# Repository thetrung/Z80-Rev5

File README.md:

# Z80-Rev5 
Rev.5 of Z80 system designed with STC8H8K64U, 512K SRAM/EEPROM.

### Note
I have never had a real working Z80 before so this board is designed to test that if I can get one.

### 3D Preview 

### Placement (SilkScreen)

### Schematic

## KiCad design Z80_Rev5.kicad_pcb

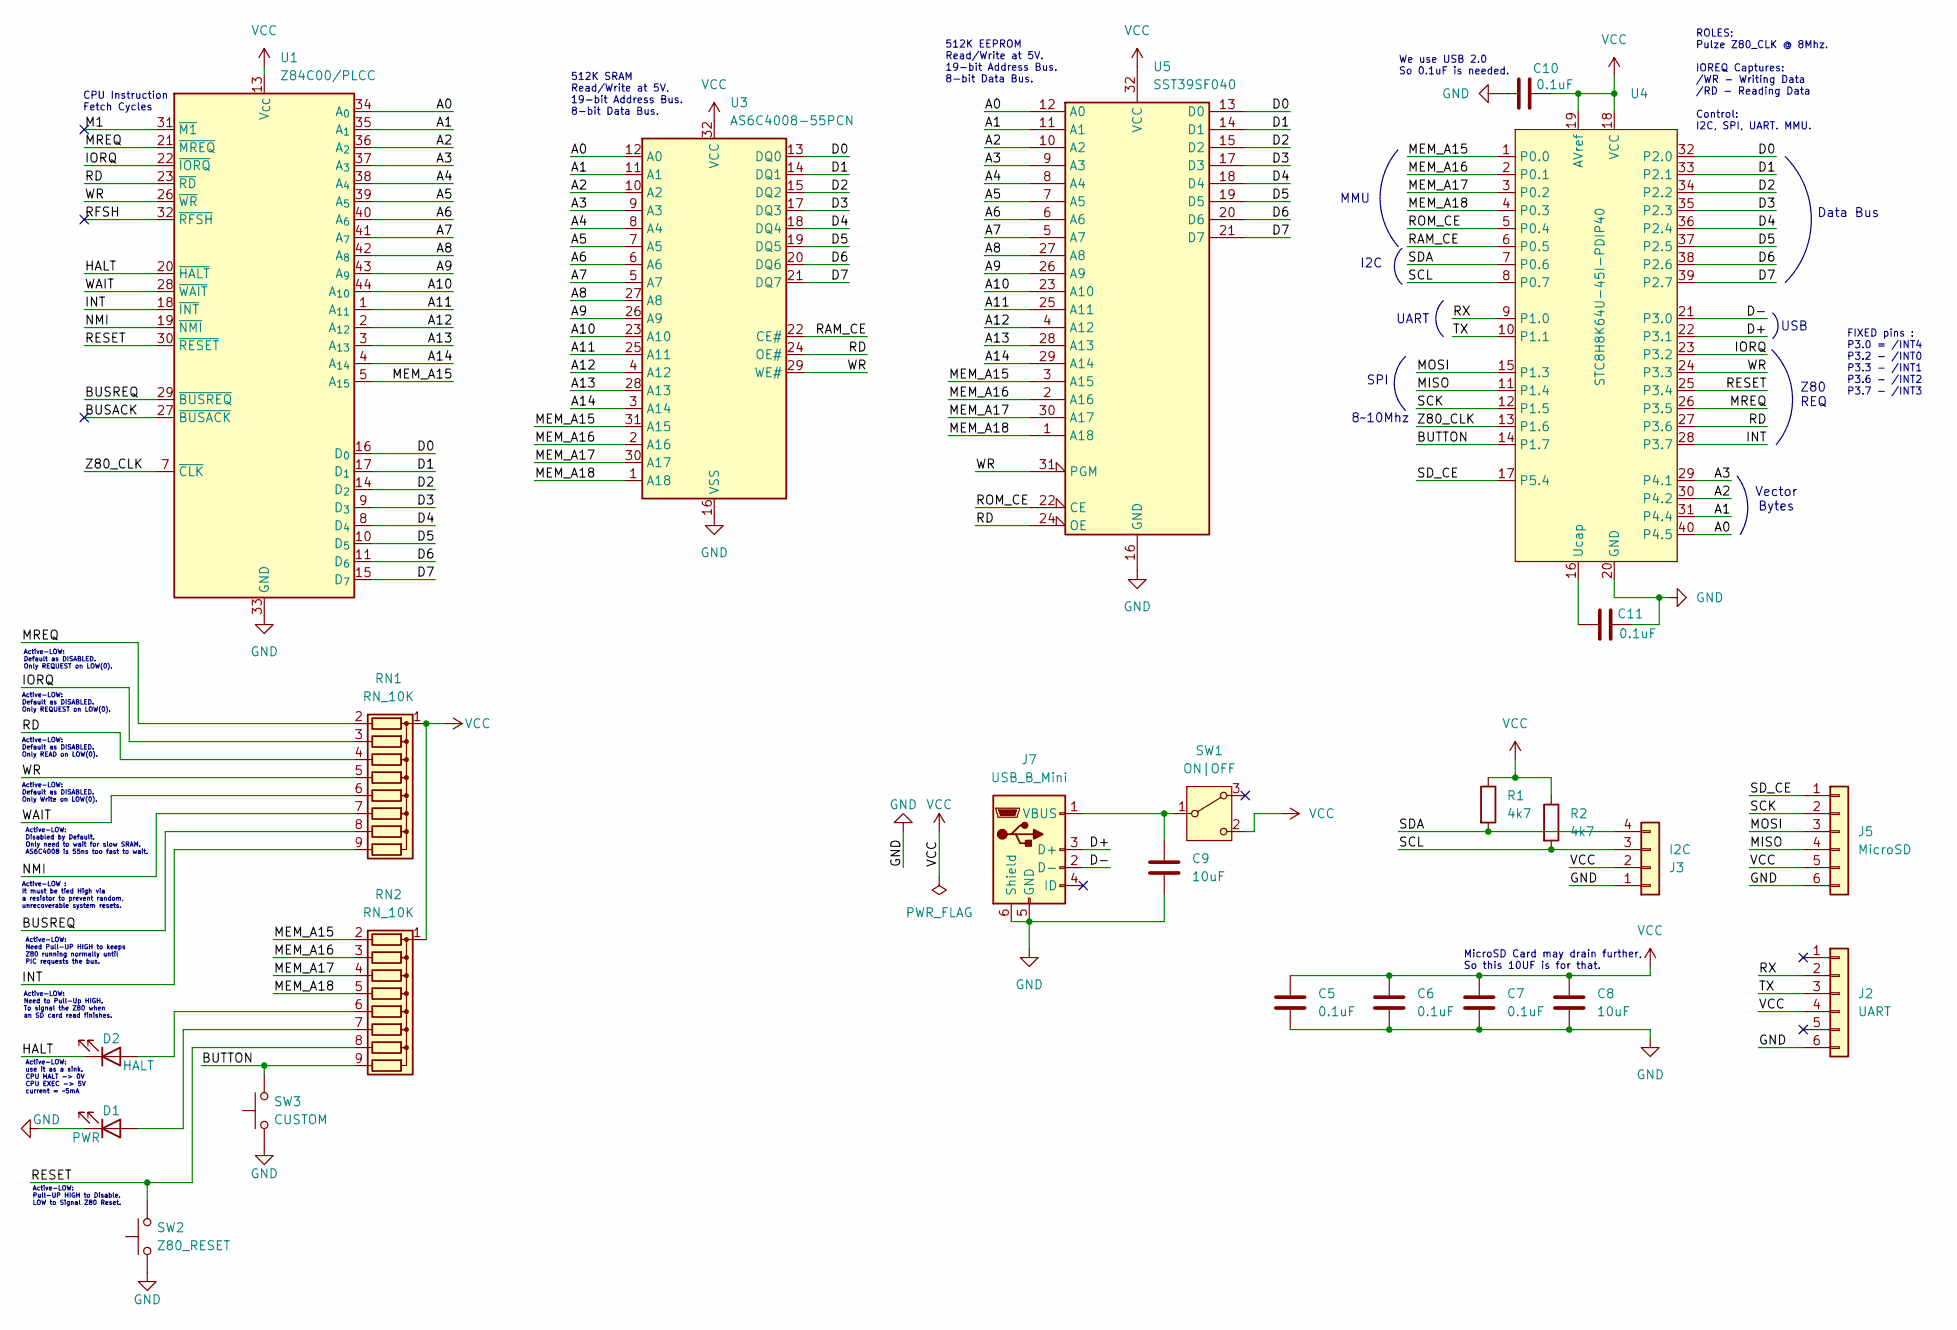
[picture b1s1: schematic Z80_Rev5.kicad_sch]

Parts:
C5, C6, C7, C10, C11: 0.1uF; C_Disc_D3.4mm_W2.1mm_P2.50mm
C8, C9: 10uF; C_Radial_D4.0mm_H5.0mm_P1.50mm
D1: PWR; LED_D3.0mm
D2: HALT; LED_D3.0mm
J2: UART; PinHeader_1x06_P2.54mm_Vertical
J3: I2C; PinHeader_1x04_P2.54mm_Vertical
J5: MicroSD; PinHeader_1x06_P2.54mm_Vertical
J7: USB_B_Mini; USB_MINI_B_90_Angled
R1, R2: 4k7; R_Axial_DIN0207_L6.3mm_D2.5mm_P10.16mm_Horizontal
RN1, RN2: RN_10K; R_Array_SIP9
SW1: ON|OFF; SW_Slide-03_Wuerth-WS-SLTV_10x2.5x6.4_P2.54mm
SW2: Z80_RESET; SW_PUSH_6mm
SW3: CUSTOM; SW_PUSH_6mm
U1: Z84C00/PLCC; PLCC-44_THT-Socket
U3: AS6C4008-55PCN; DIP-32_W15.24mm
U4: STC8H8K64U-45I-PDIP40; DIP-40_W15.24mm
U5: SST39SF040; DIP-32_W15.24mm_Socket

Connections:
/A0: U1.34 (A_{0}), U3.12 (A0), U4.40 (P4.5), U5.12 (A0)
/A1: U1.35 (A_{1}), U3.11 (A1), U4.31 (P4.4), U5.11 (A1)
/A2: U1.36 (A_{2}), U3.10 (A2), U4.30 (P4.2), U5.10 (A2)
/A3: U1.37 (A_{3}), U3.9 (A3), U4.29 (P4.1), U5.9 (A3)
/A4: U1.38 (A_{4}), U3.8 (A4), U5.8 (A4)
/A5: U1.39 (A_{5}), U3.7 (A5), U5.7 (A5)
/A6: U1.40 (A_{6}), U3.6 (A6), U5.6 (A6)
/A7: U1.41 (A_{7}), U3.5 (A7), U5.5 (A7)
/A8: U1.42 (A_{8}), U3.27 (A8), U5.27 (A8)
/A9: U1.43 (A_{9}), U3.26 (A9), U5.26 (A9)
/A10: U1.44 (A_{10}), U3.23 (A10), U5.23 (A10)
/A11: U1.1 (A_{11}), U3.25 (A11), U5.25 (A11)
/A12: U1.2 (A_{12}), U3.4 (A12), U5.4 (A12)
/A13: U1.3 (A_{13}), U3.28 (A13), U5.28 (A13)
/A14: U1.4 (A_{14}), U3.3 (A14), U5.29 (A14)
/BUSACK: U1.27 (~BUSACK)
/BUSREQ: RN1.8 (R7), U1.29 (~BUSREQ)
/BUTTON: RN2.9 (R8), SW3.2, U4.14 (P1.7)
/D0: U1.16 (D_{0}), U3.13 (DQ0), U4.32 (P2.0), U5.13 (D0)
/D1: U1.17 (D_{1}), U3.14 (DQ1), U4.33 (P2.1), U5.14 (D1)
/D2: U1.14 (D_{2}), U3.15 (DQ2), U4.34 (P2.2), U5.15 (D2)
/D3: U1.9 (D_{3}), U3.17 (DQ3), U4.35 (P2.3), U5.17 (D3)
/D4: U1.8 (D_{4}), U3.18 (DQ4), U4.36 (P2.4), U5.18 (D4)
/D5: U1.10 (D_{5}), U3.19 (DQ5), U4.37 (P2.5), U5.19 (D5)
/D6: U1.11 (D_{6}), U3.20 (DQ6), U4.38 (P2.6), U5.20 (D6)
/D7: U1.15 (D_{7}), U3.21 (DQ7), U4.39 (P2.7), U5.21 (D7)
/D+: J7.3 (D+), U4.22 (P3.1)
/D-: J7.2 (D-), U4.21 (P3.0)
/HALT: D2.1 (K), U1.20 (~HALT)
/INT: RN1.9 (R8), U1.18 (~INT), U4.28 (P3.7)
/IORQ: RN1.3 (R2), U1.22 (~IORQ), U4.23 (P3.2)
/M1: U1.31 (~M1)
/MEM_A15: RN2.2 (R1), U1.5 (A_{15}), U3.31 (A15), U4.1 (P0.0), U5.3 (A15)
/MEM_A16: RN2.3 (R2), U3.2 (A16), U4.2 (P0.1), U5.2 (A16)
/MEM_A17: RN2.4 (R3), U3.30 (A17), U4.3 (P0.2), U5.30 (A17)
/MEM_A18: RN2.5 (R4), U3.1 (A18), U4.4 (P0.3), U5.1 (A18)
/MISO: J5.4, U4.11 (P1.4)
/MOSI: J5.3, U4.15 (P1.3)
/MREQ: RN1.2 (R1), U1.21 (~MREQ), U4.26 (P3.5)
/NMI: RN1.7 (R6), U1.19 (~NMI)
/RAM_CE: U3.22 (CE#), U4.6 (P0.5)
/RD: RN1.4 (R3), U1.23 (~RD), U3.24 (OE#), U4.27 (P3.6), U5.24 (OE)
/RESET: RN2.8 (R7), SW2.2, U1.30 (~RESET), U4.25 (P3.4)
/RFSH: U1.32 (~RFSH)
/ROM_CE: U4.5 (P0.4), U5.22 (CE)
/RX: J2.2, U4.9 (P1.0)
/SCK: J5.2, U4.12 (P1.5)
/SCL: J3.3, R2.2, U4.8 (P0.7)
/SDA: J3.4, R1.2, U4.7 (P0.6)
/SD_CE: J5.1, U4.17 (P5.4)
/TX: J2.3, U4.10 (P1.1)
/WAIT: RN1.6 (R5), U1.28 (~WAIT)
/WR: RN1.5 (R4), U1.26 (~WR), U3.29 (WE#), U4.24 (P3.3), U5.31 (PGM)
/Z80_CLK: U1.7 (~CLK), U4.13 (P1.6)
GND: C5.1, C6.1, C7.1, C8.1, C9.1, C10.2, C11.2, D1.1 (K), J2.6, J3.1, J5.6, J7.5 (GND), J7.6 (Shield), SW2.1, SW3.1, U1.33 (GND), U3.16 (VSS), U4.20 (GND), U5.16 (GND)
unnamed: D1.2 (A), RN2.7 (R6)
unnamed: D2.2 (A), RN2.6 (R5)
unnamed: C9.2, J7.1 (VBUS), SW1.1 (B)
unnamed: C11.1, U4.16 (Ucap)
VCC: C5.2, C6.2, C7.2, C8.2, C10.1, J2.4, J3.2, J5.5, R1.1, R2.1, RN1.1 (common), RN2.1 (common), SW1.2 (C), U1.13 (V_{CC}), U3.32 (VCC), U4.18 (VCC), U4.19 (AVref), U5.32 (VCC)

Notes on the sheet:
Active-LOW: Default as DISABLED. Only REQUEST on LOW(0).
Active-LOW: Need to Pull-Up HIGH. To signal the Z80 when an SD card read finishes.
Data Bus
512K SRAM Read/Write at 5V. 19-bit Address Bus. 8-bit Data Bus.
Active-LOW: use it as a sink. CPU HALT -> 0V CPU EXEC -> 5V current = ~5mA
Active-LOW: Default as DISABLED. Only READ on LOW(0).
UART
MMU
ROLES: Pulze Z80_CLK @ 8Mhz. IOREQ Captures: /WR - Writing Data /RD - Reading Data Control: I2C, SPI, UART. MMU.
512K EEPROM Read/Write at 5V. 19-bit Address Bus. 8-bit Data Bus.
Active-LOW: Disabled by Default. Only need to wait for slow SRAM. AS6C4008 is 55ns too fast to wait.
Active-LOW: Need Pull-UP HIGH to keeps Z80 running normally until PIC requests the bus.
Vector Bytes
MicroSD Card may drain further, So this 10UF is for that.
Active-LOW : It must be tied High via a resistor to prevent random, unrecoverable system resets.
Active-LOW: Pull-UP HIGH to Disable. LOW to Signal Z80 Reset.
Active-LOW: Default as DISABLED. Only Write on LOW(0).
Z80 REQ
FIXED pins : P3.0 = /INT4 P3.2 - /INT0 P3.3 - /INT1 P3.6 - /INT2 P3.7 - /INT3
8~10Mhz
We use USB 2.0 So 0.1uF is needed.
CPU Instruction Fetch Cycles
USB
I2C
SPI

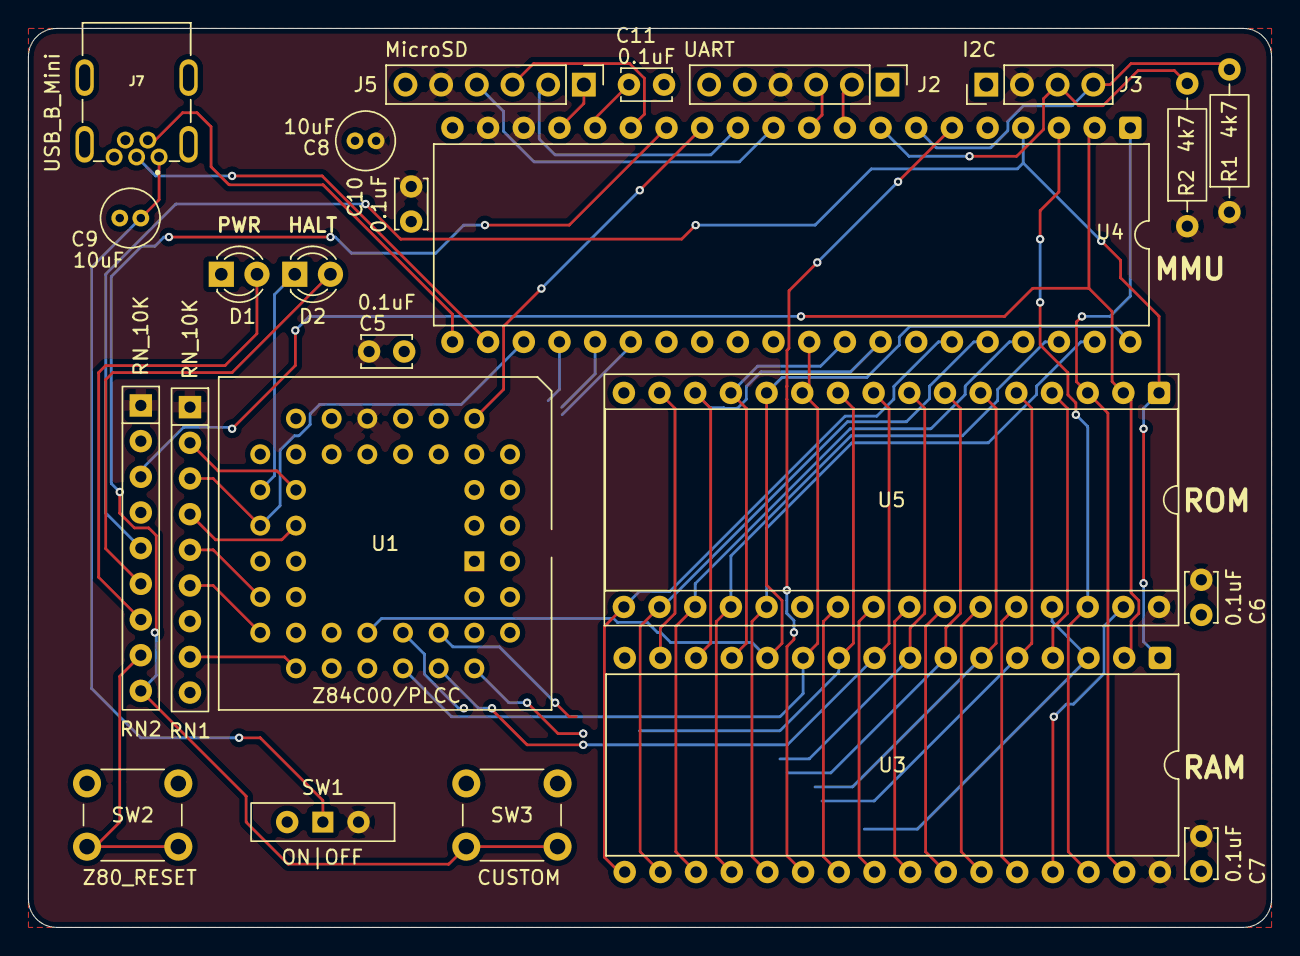
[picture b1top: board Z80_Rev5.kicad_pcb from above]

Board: 2 copper layers, 88.5 x 64.0 mm, 24 parts (0 on the bottom side), 57 nets.
